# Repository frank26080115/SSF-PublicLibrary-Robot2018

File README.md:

# SSF-PublicLibrary-Robot2018

This repo contains the hardware, software, and courseware of a small robotics STEM education program. This program is targeting ages 12+, involves 3 live classes held at South San Francisco Public Library, and a robot that's insanely cheap but also incredibly educational.

Perhaps the data here is useful for other educational organizations on a budget.

Please click "Clone or Download" and then "Download ZIP". When the ZIP file is downloaded, unzip it somewhere and open "courseware/index.htm" with a web browser. This will start the course. All the courseware is written as web pages, with pictures, videos, and interactive demos.

The lessons are also hosted on my own website, http://eleccelerator.com/ssfpl_robotics_class_2018/

## Software Required

- Arduino 1.8.1 (this is what SSF Public Library has currently installed)
- Onshape account (free web browser based CAD software that mimics SolidWorks)

## Thanks to: [Microchip Technology](https://www.microchip.com/)

A big thanks to [Microchip Technology](https://www.microchip.com/). These guys manufacture the chip in the middle of your Arduino. My professional contacts at their local office generously donated an insane amount of screwdrivers and backpacks. These classes would not have been possible without their help. Their kindness will not be forgotten.

Personally I thank Microchip for jumpstarting my own path in this hobby and career. Microchip Technology is a huge supporter of STEM programs, I definitely have many of their dev kits simply because they handed them out to me in university. Even when I was a poor highschooler, I got started with their PIC microcontrollers because they were essentially free. I truly believe they are the reason why I am insanely good at writing low-level bare-metal embedded firmware. By the time Arduino Diecimila (the first Arduino with USB) was available, I immediately outgrew the Arduino IDE because of just how far using a PIC has pushed me.

## Thanks to: [Adafruit Industries](https://www.adafruit.com/)

[Adafruit Industries](https://www.adafruit.com/) is a founding pillar of the maker movement from the very beginning, and a [champion for women engineers and entrepreneurs](https://www.adafruit.com/about). Limor "Ladyada" Fried and Phillip Torrone (former senior editor at Make: Magazine, Hackaday, Popular Science, Howtoons) donated all the soldering irons we need that makes these classes possible. These irons are the good stuff, coated tips, adjustable ceramic heaters, fire-proof wiring!

As a huge supporter of STEAM education, Adafruit Industries have written literally [thousands of guides and tutorials](https://learn.adafruit.com/), along side their amazing collection of products that makes it easy for everyday people to accomplish what used to be impossible. How do I know they are so good? I used to work for Adafruit myself, I wrote some of those tutorials and designed some of those products. Even today my real job's engineering department use their stuff regularly, their breakout boards are just so convenient for quick prototypes. Everything is manufactured proudly on home turf in their New York City office. I recommend all hobbyists to follow [their blog](https://blog.adafruit.com/), it's a good mix of electronics, 3D printing, art, and other fun news.

## Thanks to: [PCBWay](https://www.pcbway.com/)

[PCBWay](https://www.pcbway.com/) is a speedy and cheap PCB manufacturer and electronics assembly company. They generously provided us with multi-colour PCBs for free, so your robots can be pretty and more unique.

Their service is speedy and at a price that was unheard of before the maker movement took off, making it more accessible to hobbyists and students, allowing the little guys to keep up with the big tech companies. PCBWay also do a lot of [community outreach](https://www.pcbway.com/project/sponsor/) to hobbyists and student teams, hosting contests and offering sponsorships.

Their PCBs are pretty high quality, there's nothing to complain about. Great looking silkscreen. Soldermask and drills are on point. Edges are milled clean. No splatter with the plating. No hassle using their website to order. Each one of our robot PCBs would cost roughly $3.50 each including shipping, and take one week from time-of-order to your doorstep. Great job PCBWay.

## Thanks to: [Silicon Labs](https://www.silabs.com/)

I reached out to people I know at the local [Silicon Labs](https://www.silabs.com/) office, and they gave us a big box of goodies to encourage people to participate in STEM programs at our library.

They are a company who manufacture a lot of different microchips, such as the USB interface chips that hobbyists often use to debug the Raspberry Pi and other embedded Linux platforms. If you are into the drone racing hobby, most likely your drone already has four microcontrollers made by Silicon Labs. They've been growing rapidly in the past decade and is currently well known for having unique, high performance, and low power products, as well as legacy products that are solid and dirt cheap.

## Thanks to: [Hackaday](https://hackaday.com/)

Hackaday always have a special place in my life, providing me with constant motivation and keeping me up-to-date on both my hobby and professional life. They are literally the biggest reason why I am working a dream job in sunny California. I think their blog is inspirational to everybody here and so they gave me a pile of stickers to give to my class!

They are the host of an excellent online community at [Hackaday.io](https://hackaday.io/), hosts awesome events such as the [Hackaday SuperConference](https://hackaday.com/tag/hackaday-superconference/) and their [Hackaday Prize](https://hackaday.io/prize), and also they run the beloved [Tindie](https://www.tindie.com/) where creative makers and hackers can sell their creations.

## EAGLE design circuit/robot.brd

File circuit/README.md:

This directory contains the circuit schematic, PCB layout, and PCB gerber files for the robot's circuit board.

The file formats are for CadSoft EAGLE 6.4.0

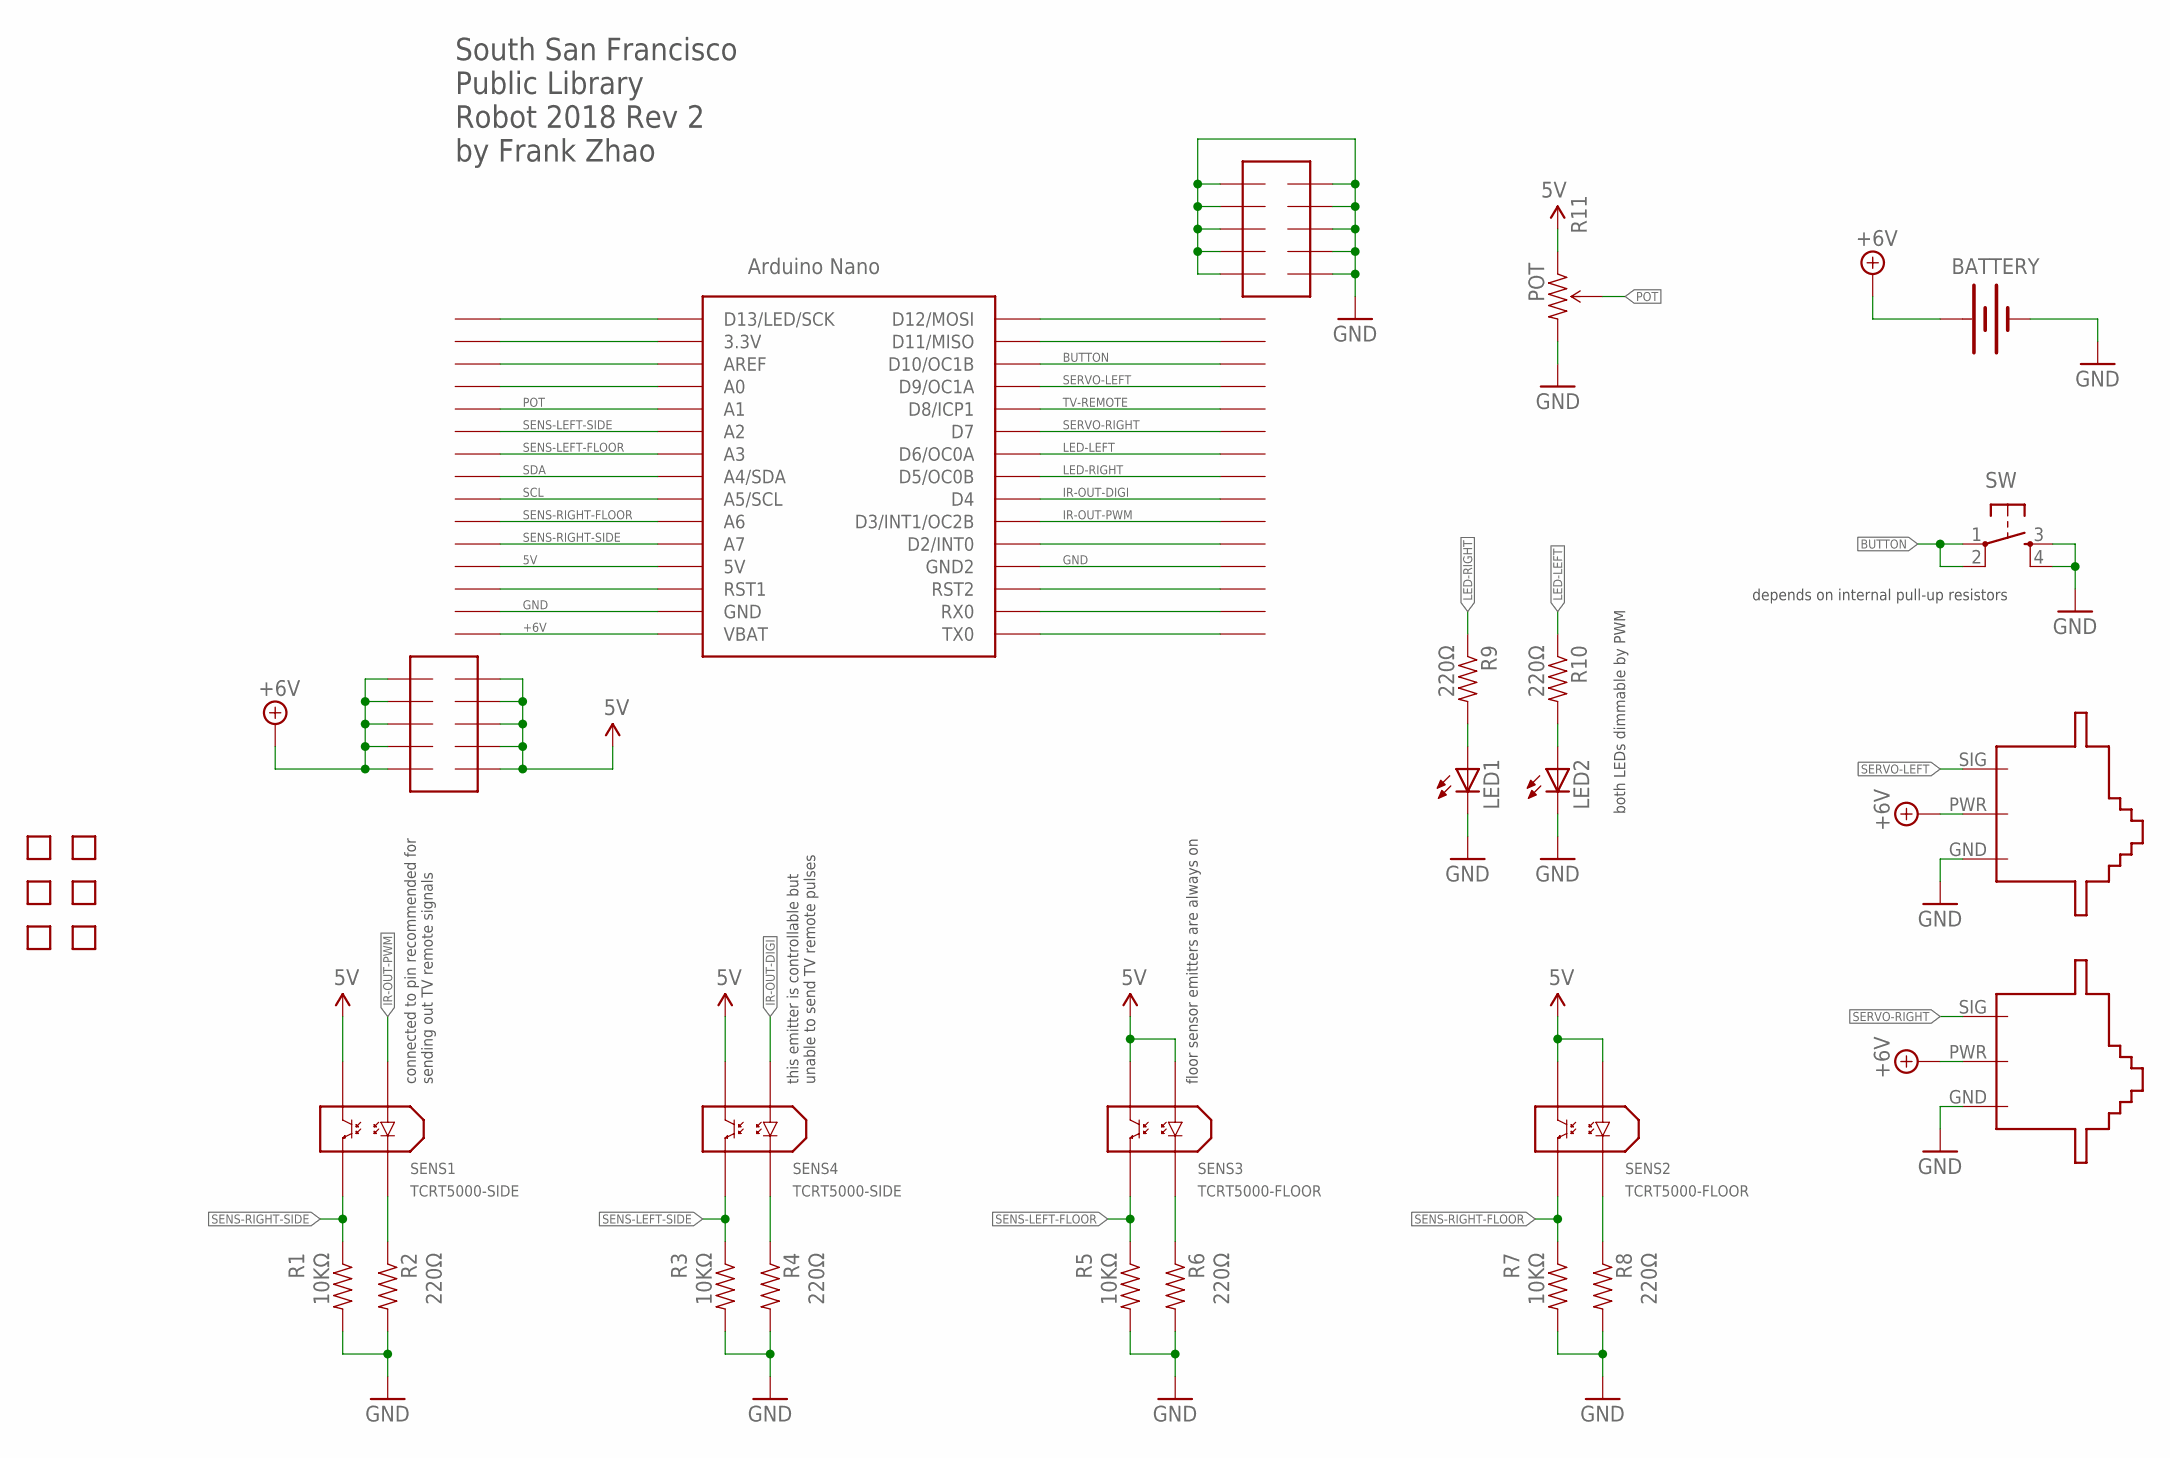
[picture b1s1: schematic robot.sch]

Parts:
BATTERY: BATTERY-WIRE-CONN; BATT-WIRE-CONN
LED1, LED2: LED5MM
M1: SERVO-FLIPPED
M2: SERVO-1; SERVO
R1, R3, R5, R7: 10KΩ; AXIAL-0.3
R2, R4, R6, R8, R9, R10: 220Ω; AXIAL-0.3
R11: POT; TRIM_POT_PTH
SENS1, SENS4: TCRT5000-SIDE
SENS2, SENS3: TCRT5000-FLOOR
SW: TAC_SWITCHPTH; TACTILE-PTH
U5: NANO
U$1: ROBOT-BODY-HOLDER
U$8: PROTO-AREA-MID; PROTO-AREA-1
U$9: TEXT-INFO
U$10, U$11, U$12, U$13: HOLE; HOLE-2MM
X1, X2: NANO-HEADER-SURROUND

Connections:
5V: R11.1 (CCW), SENS1.COL, SENS2.AN, SENS2.COL, SENS3.AN, SENS3.COL, SENS4.COL, U5.5V, X2.4, X2.E6, X2.E7, X2.E8, X2.E9, X2.E10
+6V: BATTERY.POS (+), M1.PWR, M2.PWR, U5.RAW (VBAT), X2.1, X2.E1, X2.E2, X2.E3, X2.E4, X2.E5
A0: U5.A0, X2.12
BUTTON: SW.1, SW.2, U5.D10 (D10/OC1B), X1.3
GND: BATTERY.NEG (-), LED1.K (C), LED2.K (C), M1.GND, M2.GND, R1.P$2 (2), R2.P$2 (2), R3.P$2 (2), R4.P$2 (2), R5.P$2 (2), R6.P$2 (2), R7.P$2 (2), R8.P$2 (2), R11.3 (CW), SW.3, SW.4, U5.GND, U5.GND1 (GND2), X1.12, X1.E1, X1.E2, X1.E3, X1.E4, X1.E5, X1.E6, X1.E7, X1.E8, X1.E9, X1.E10, X2.2
IR-OUT-DIGI: SENS4.AN, U5.D4, X1.9
IR-OUT-PWM: SENS1.AN, U5.D3 (D3/INT1/OC2B), X1.10
LED-LEFT: R10.P$1 (1), U5.D6 (D6/OC0A), X1.7
LED-RIGHT: R9.P$1 (1), U5.D5 (D5/OC0B), X1.8
unnamed: R2.P$1 (1), SENS1.CAT
unnamed: R4.P$1 (1), SENS4.CAT
unnamed: R6.P$1 (1), SENS3.CAT
unnamed: R8.P$1 (1), SENS2.CAT
unnamed: LED1.A, R9.P$2 (2)
unnamed: LED2.A, R10.P$2 (2)
unnamed: U5.3.3V, X2.14
unnamed: U5.AREF, X2.13
unnamed: U5.RST (RST1), X2.3
unnamed: U5.D13 (D13/LED/SCK), X2.15
unnamed: U5.D12 (D12/MOSI), X1.1
unnamed: U5.D11 (D11/MISO), X1.2
unnamed: U5.D2 (D2/INT0), X1.11
unnamed: U5.RST1 (RST2), X1.13
unnamed: U5.RX0, X1.14
unnamed: U5.TX0, X1.15
POT: R11.2 (WIPER), U5.A1, X2.11
SCL: U5.A5 (A5/SCL), X2.7
SDA: U5.A4 (A4/SDA), X2.8
SENS-LEFT-FLOOR: R5.P$1 (1), SENS3.EM, U5.A3, X2.9
SENS-LEFT-SIDE: R3.P$1 (1), SENS4.EM, U5.A2, X2.10
SENS-RIGHT-FLOOR: R7.P$1 (1), SENS2.EM, U5.A6, X2.6
SENS-RIGHT-SIDE: R1.P$1 (1), SENS1.EM, U5.A7, X2.5
SERVO-LEFT: M2.SIG, U5.D9 (D9/OC1A), X1.4
SERVO-RIGHT: M1.SIG, U5.D7, X1.6
TV-REMOTE: U5.D8 (D8/ICP1), X1.5

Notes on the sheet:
connected to pin recommended for sending out TV remote signals
this emitter is controllable but unable to send TV remote pulses
floor sensor emitters are always on
depends on internal pull-up resistors
both LEDs dimmable by PWM

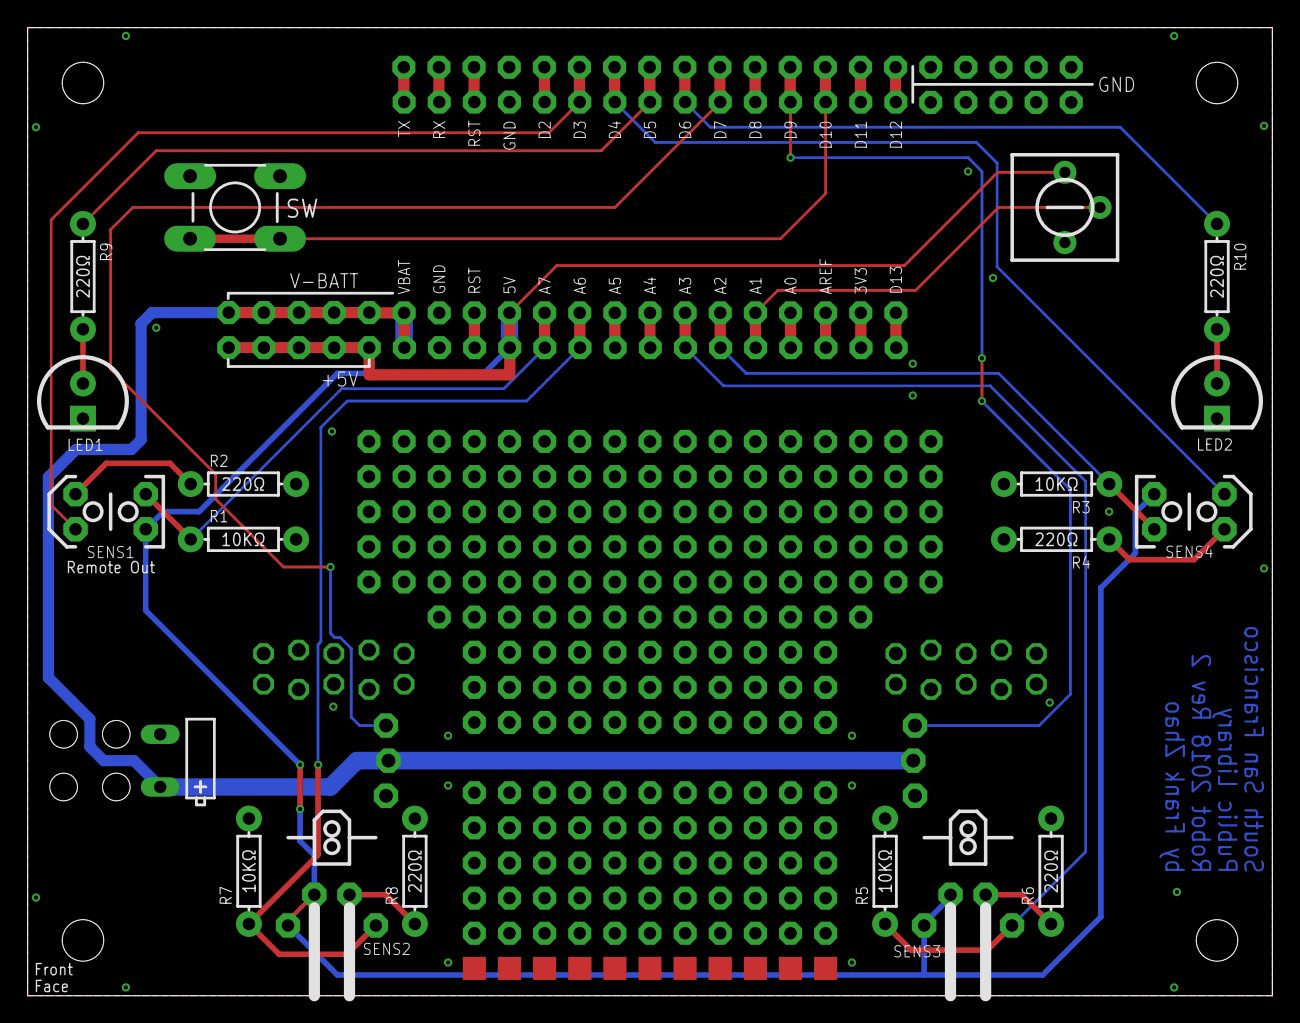
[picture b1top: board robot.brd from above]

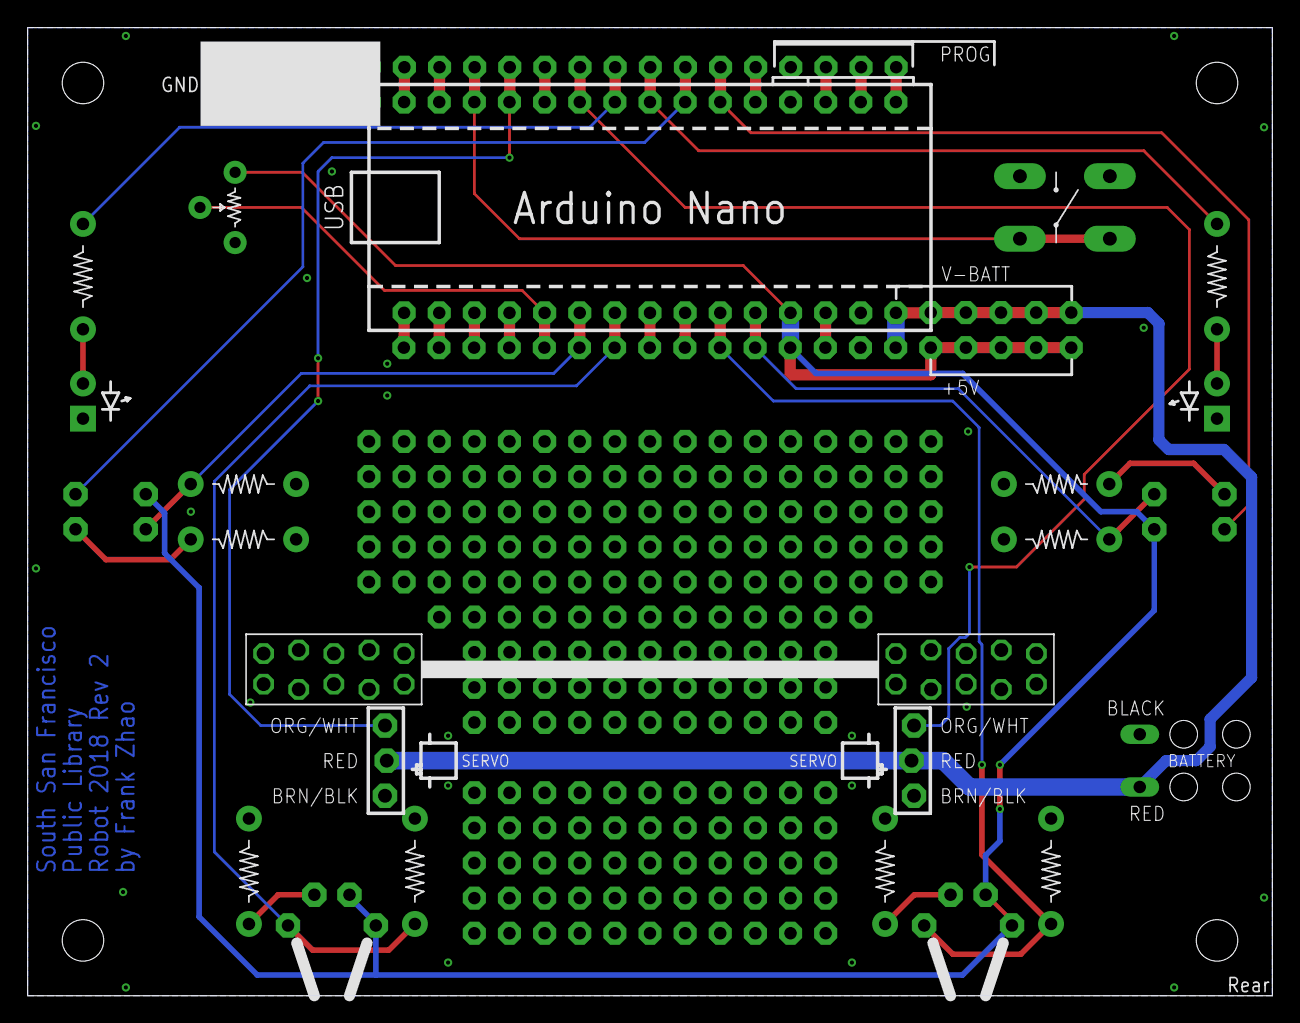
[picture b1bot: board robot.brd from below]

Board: 2 copper layers, 90.0 x 70.0 mm, 31 parts (7 on the bottom side), 35 nets.

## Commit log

2018-04-16 initial commit
    some readmes, some arduino libs, all elec
2018-04-18 continousservo accel works, added IR codes
    continuous servo works
2018-04-18 added unmodified optiboot
2018-04-18 new bootloader with button hold
2018-04-19 LUFA and USB2Serial unmodified
2018-04-19 kitprog as usb2serial
2018-04-19 bootloadable usb2ser rebuild settings
2018-04-19 add ext reset to avr usb2ser
2018-04-19 readme for dongle
2018-04-19 avr usb2ser improve usb response
2018-04-19 psoc dongle fully working and tested
2018-04-20 removed AVR USB2UART dongle
2018-04-20 no need for bootloader mod anymore
    because the dongle has autoreset
2018-04-20 working demo with TV remote done
2018-04-21 real Arduino VID PID used
    previous one pulled from repo was not real
2018-04-21 updated baud rate for dongle
2018-04-21 update default debug baud to match dongle
2018-04-21 attempt for dongle to change baud realtime
2018-04-21 added parity bits change to dongle
    fixed prevbaud not changing
    removed PSoC3 and PSoC4
2018-04-22 robo demo at library
2018-05-03 dongle RX pin changed to pull-up resistor
2018-05-04 circuit error: flipped floor sensor footprint
2018-05-05 adding PID arduino library
2018-05-05 changes to servo code, added IMU code, other small changes
    added back LED
    not tested but compiles without error
2018-05-12 3D modelling class content almost done
2018-05-14 start of circuit basics class
2018-05-16 single sensor test rig
2018-05-16 almost finalized 3D CAD class
2018-05-16 circuit lesson contents
2018-05-17 elec class and assembly class
2018-05-17 removing thumbs.db
2018-05-17 adjusted soldering diagram
2018-05-19 more class content
2018-05-19 additional class content
    heavy usage of EveryCircuit
2018-05-20 more class content
    desoldering 2, tires, breadboard
2018-05-21 incomplete class content for Arduino
2018-05-21 new soldering graphics
2018-05-23 code inline documentation to match lesson
2018-05-23 course concent
2018-05-24 small bit more class content
    colour spectrum, excercise 2 flow chart
2018-05-24 delay after emitters on/off
2018-05-24 minor readme correction
2018-05-24 few more screenshots
    also fixed colour spectrum image
2018-05-24 bad link to colour spectrum
2018-05-25 more class content
    dongle images, smaller screenshots, gif of LED blinking
2018-05-25 minor class content changes
2018-05-25 better peeling picture
2018-05-25 adjustment to soldering comic instructions
2018-05-25 organizing the foreword stuff
2018-05-26 almost done arduino class
2018-05-26 added index page, minor lesson changes
2018-05-26 missed a picture about nano vs uno
2018-05-27 serial added to hardware test code
2018-05-27 gfx for arduino nano pinout
2018-05-27 breadboard gfx
2018-05-27 muted videos inside arduino class
2018-05-27 renamed extra class, more content
2018-05-27 removed audio from demo vids
2018-05-28 more course content, IR remote, PCBs, and others
2018-05-29 sketches changed to align with lessons
2018-05-29 renamed IR emitter functions, for easier understanding
2018-05-29 flip one servo for corrected drive direction
2018-05-29 extra lesson content
2018-05-29 changes to PCB information
2018-05-29 made exercise 2 easier
2018-05-29 added finished robot and PCB images
2018-05-29 reduced scope of extra class
2018-05-29 added line following video
2018-05-29 fixed links in Arduino class
2018-05-29 update to reflect Microchip's donation
2018-05-29 small edits to meta information
2018-05-29 lesson footer added link
2018-05-30 added some more code comments
2018-05-30 added wallavoider and serialportdemo
2018-05-30 flashlights
2018-05-30 added missing blinking test, added github links
2018-05-30 unicode madness
2018-05-30 mobile browser rendering bug
2018-05-30 adding syntax highlighter
2018-05-30 starting the controlling tv lesson
2018-05-30 course content for controlling tv
2018-05-30 github logo
2018-05-30 minor text edits
2018-05-30 search_in_files image
2018-05-31 remote control demo video
2018-05-31 add demo vids to front page
2018-05-31 ir out pin gfx, more websites to learn from, fixed a typo
2018-05-31 start circuit lesson with a finished picture
2018-05-31 vid edited to prevent control bar cutoff
2018-05-31 video re-encode for various problems
2018-05-31 removed vid ctrl from a loop, added wiki link to Hz
2018-06-02 new lesson on ohms law
2018-06-02 added breadboarded nano pic
2018-06-02 gif to download video
2018-06-02 made placeholders for videos better
2018-06-03 sponsor blob, added adafruit but hidden until pics
2018-06-05 more circuit gifs
2018-06-06 replaced everycircuit embeds with GIFs
2018-06-07 adding Adafruit to sponsors
2018-06-08 convenient zip file for another production run
2018-06-08 Race Referee code, tested
2018-06-08 minor sponsor edit
2018-06-09 new promo video
2018-06-09 typo
2018-06-13 edited sponsor, added PCBWay, better photos
2018-06-13 minor change to PCBWay blurb
2018-06-15 Thanks to Silicon Labs
2018-06-15 readme now has images and links
2018-06-18 Bluefruit code working and tested
2018-06-18 colourful neopixels for bluetooth demo
2018-06-19 bluetooth demo turned too slow
2018-06-19 restored IR remote pin default pull resistor
2018-06-20 start of referee page
2018-06-20 more referee page stuff
2018-06-22 extra project content
2018-06-22 almost finished extra project content
2018-06-22 tiny pcbway blurb edit
2018-06-22 front page edits
2018-06-22 printable URL, other robot competitions, minor front page changes
2018-06-26 grammar edits
2018-06-26 grammar edit
2018-06-29 convert onshape accnts to metric
2018-06-30 got rid of unfinished arduino code files
2018-07-02 before class
2018-07-04 missed a renamed function call
2018-07-05 added image illustrating differentt parts
2018-07-05 cleaner images
2018-07-06 3d printed wheel
2018-07-06 added temporary no pulse for servo stop
2018-07-06 another line for solder safety
2018-07-06 fixed cont. servo calib. tool bug with no-pulse default
2018-07-09 housekeeping vid was missing click effects
2018-07-09 the name of this file triggers adblockers
2018-07-09 reminder for missing line during mirror
2018-07-09 out-of-place sentence
2018-07-09 corrected order of hole creation in CAD class
2018-07-09 alternative pin slot video, shortened prev vid too
2018-07-09 added 3D CAD mouse tutorial
2018-07-09 explain Onshape's constraints toolbar hidden list
2018-07-10 added video on fixing small mistakes on onshape
2018-07-10 added video covering confusion with right click in onshape
2018-07-10 note for when the battery holder has different holes
2018-07-10 made circuit advanced class more prominent
2018-07-10 another image to show where the robot body model is
2018-07-11 mech changes, added wheels, added more gcode
2018-07-12 wrong file name
2018-07-12 better images involving headers soldering
2018-07-12 attempted to clean pic
2018-07-12 images to show finished solder joints
2018-07-12 image for resistor values
2018-07-13 rechargable batteries lesson start
2018-07-13 instruction to snip excess leads
2018-07-14 more info in rechargable battery page
2018-07-16 10kohm resistor image was wrong
2018-07-16 new pic for front page, and added rechargable battery class link
2018-07-16 more verbose instruction on header soldering
2018-07-17 added untested hexbug IR code
2018-07-17 fixed bug with no pulse on stop for servos
2018-07-17 updated bit on rechargable AAs
2018-07-17 HEXBUG receiver working
2018-07-22 added image for resistor soldering instructions
2018-07-30 new images regarding servo installation
2018-08-03 instructions for mac arduino drivers
2018-08-03 bad div element
2018-08-05 added another mistake prevention image to CAD class
2018-08-05 thanks Hackaday!
2018-08-06 better hackaday image
2018-08-14 added another circuit homework question
